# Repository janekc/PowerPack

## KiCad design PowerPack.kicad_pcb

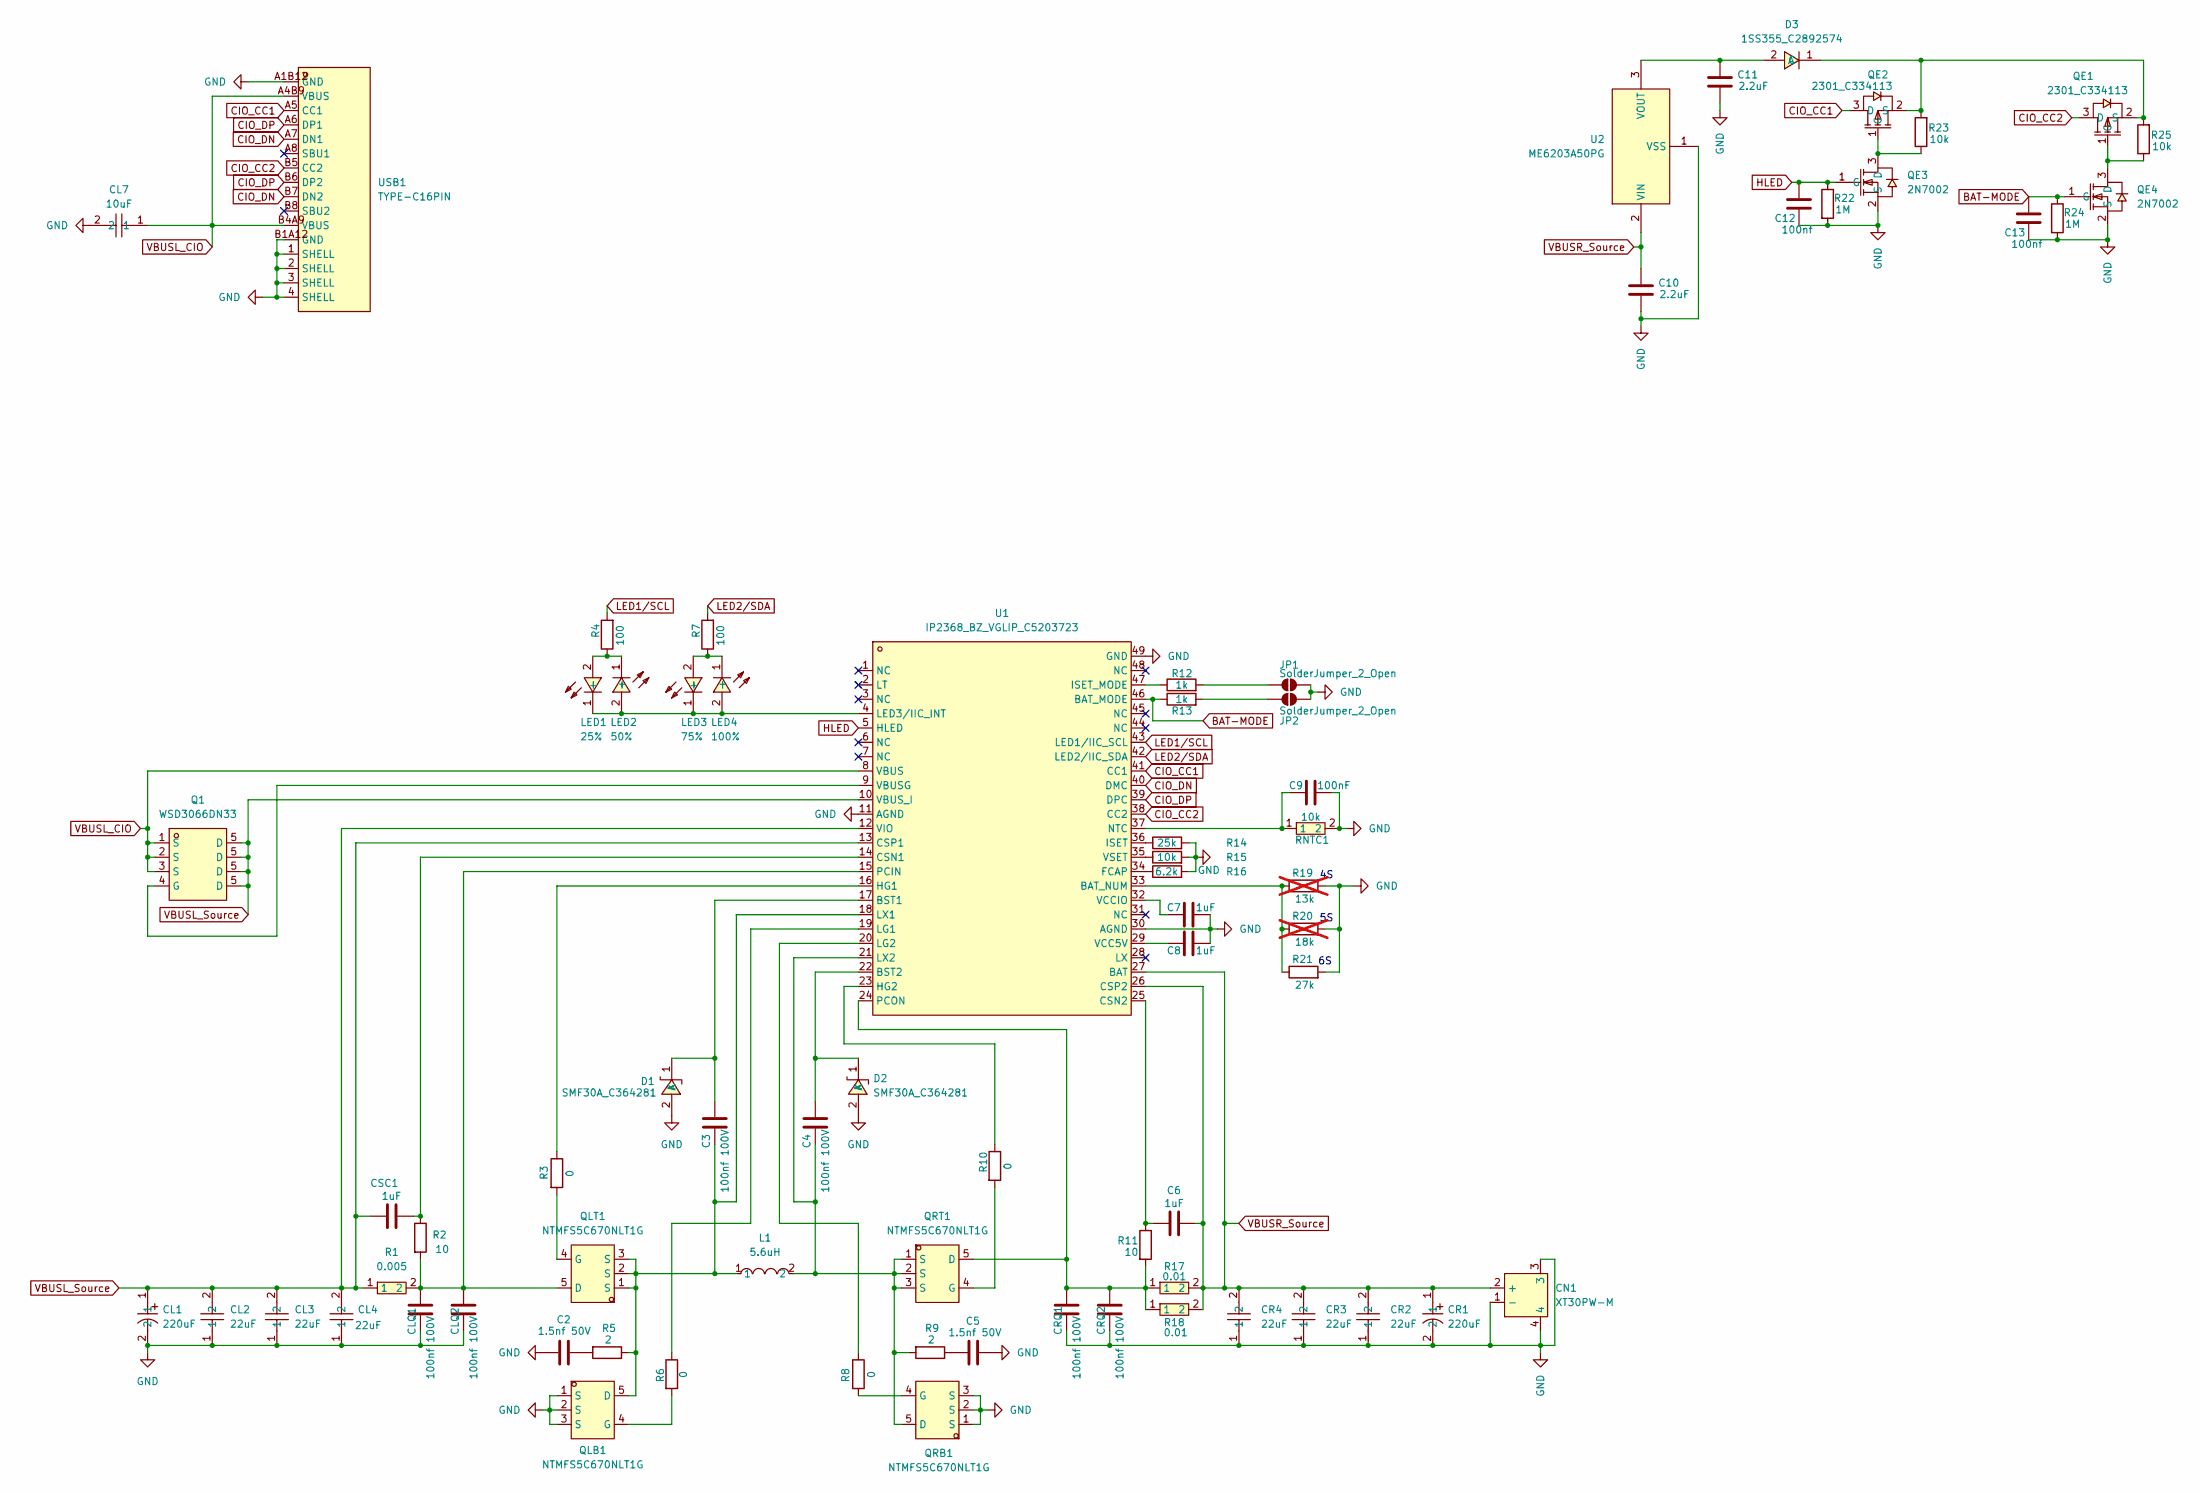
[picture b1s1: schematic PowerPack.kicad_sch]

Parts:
C2, C5: 1.5nf 50V; C_0402_1005Metric_Pad0.74x0.62mm_HandSolder
C3, C4: 100nf 100V; C_0402_1005Metric_Pad0.74x0.62mm_HandSolder
C6, C7, C8: 1uF; C_0402_1005Metric_Pad0.74x0.62mm_HandSolder
C9: 100nF; C_0603_1608Metric_Pad1.08x0.95mm_HandSolder
C10, C11: 2.2uF; C_0402_1005Metric_Pad0.74x0.62mm_HandSolder
C12, C13: 100nf; C_0402_1005Metric_Pad0.74x0.62mm_HandSolder
CL1: 220uF; CAP-TH_BD8.0-P3.50-D0.6-FD; LCSC Part C2688260
CL2, CL3, CL4: 22uF; C1210; LCSC Part C778721
CL7: 10uF; C1206; LCSC Part C76715
CLQ1, CLQ2: 100nf 100V; C_0402_1005Metric_Pad0.74x0.62mm_HandSolder
CN1: XT30PW-M; CONN-TH_XT30PW-M; LCSC Part C431092
CR1: 220uF; CAP-TH_BD8.0-P3.50-D0.6-FD; LCSC Part C2688260
CR2, CR3, CR4: 22uF; C1210; LCSC Part C778721
CRQ1, CRQ2: 100nf 100V; C_0402_1005Metric_Pad0.74x0.62mm_HandSolder
CSC1: 1uF; C_0402_1005Metric_Pad0.74x0.62mm_HandSolder
D1, D2: SMF30A_C364281; SOD-123_L2.6-W1.6-LS3.5-RD; LCSC Part C364281
D3: 1SS355_C2892574; SOD-323_L1.8-W1.3-LS2.5-RD; LCSC Part C2892574
JP1, JP2: SolderJumper_2_Open; SolderJumper-2_P1.3mm_Open_RoundedPad1.0x1.5mm
L1: 5.6uH; IND-SMD_L13.4-W12.6; LCSC Part C408522
LED1: 25%; LED0603-RD; LCSC Part C84265
LED2: 50%; LED0603-RD; LCSC Part C84265
LED3: 75%; LED0603-RD; LCSC Part C84265
LED4: 100%; LED0603-RD; LCSC Part C84265
Q1: WSD3066DN33; DFN-8_L3.3-W3.3-P0.65-BL; LCSC Part C148386
QE1, QE2: 2301_C334113; SOT-23_L2.9-W1.3-P1.90-LS2.4-BR; LCSC Part C334113
QE3, QE4: 2N7002; SOT-23-3_L2.9-W1.3-P1.90-LS2.4-BR; LCSC Part C8545
QLB1: NTMFS5C670NLT1G; DFN-5_L6.1-W5.1-P1.27-BL; LCSC Part C179626
QLT1: NTMFS5C670NLT1G; DFN-5_L6.1-W5.1-P1.27-BL; LCSC Part C179626
QRB1: NTMFS5C670NLT1G; DFN-5_L6.1-W5.1-P1.27-BL; LCSC Part C179626
QRT1: NTMFS5C670NLT1G; DFN-5_L6.1-W5.1-P1.27-BL; LCSC Part C179626
R1: 0.005; R1206; LCSC Part C723403
R2, R11: 10; R_0402_1005Metric_Pad0.72x0.64mm_HandSolder
R3, R6, R8, R10: 0; R_0603_1608Metric_Pad0.98x0.95mm_HandSolder
R4, R7: 100; R_0402_1005Metric_Pad0.72x0.64mm_HandSolder
R5, R9: 2; R_0402_1005Metric_Pad0.72x0.64mm_HandSolder
R12, R13: 1k; R_0402_1005Metric_Pad0.72x0.64mm_HandSolder
R14: 25k; R_0402_1005Metric_Pad0.72x0.64mm_HandSolder
R15, R23, R25: 10k; R_0402_1005Metric_Pad0.72x0.64mm_HandSolder
R16: 6.2k; R_0402_1005Metric_Pad0.72x0.64mm_HandSolder
R17, R18: 0.01; R1206; LCSC Part C105362
R19: 13k; R_0402_1005Metric_Pad0.72x0.64mm_HandSolder; not fitted
R20: 18k; R_0402_1005Metric_Pad0.72x0.64mm_HandSolder; not fitted
R21: 27k; R_0402_1005Metric_Pad0.72x0.64mm_HandSolder
R22, R24: 1M; R_0402_1005Metric_Pad0.72x0.64mm_HandSolder
RNTC1: 10k; R0603; LCSC Part C98220
U1: IP2368_BZ_VGLIP_C5203723; QFN-48_L7.0-W7.0-P0.50-TL-EP5.4-1; LCSC Part C5203723
U2: ME6203A50PG; SOT-89_L4.5-W2.5-P1.50-LS4.2-BR; LCSC Part C94056
USB1: TYPE-C16PIN; USB-C-SMD_TYPE-C16PIN; LCSC Part C393939

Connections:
BAT-MODE: C13.2, QE4.1 (G), R13.1, R24.1, U1.46 (BAT_MODE)
CIO_CC1: QE2.3 (D), U1.41 (CC1), USB1.A5 (CC1)
CIO_CC2: QE1.3 (D), U1.38 (CC2), USB1.B5 (CC2)
CIO_DN: U1.40 (DMC), USB1.A7 (DN1), USB1.B7 (DN2)
CIO_DP: U1.39 (DPC), USB1.A6 (DP1), USB1.B6 (DP2)
GND: C2.1, C5.2, C7.2, C8.2, C9.2, C10.1, C11.1, C12.1, C13.1, CL1.2, CL2.1, CL3.1, CL4.1, CL7.2, CLQ1.2, CLQ2.2, CN1.1 (-), CN1.3, CN1.4, CR1.2, CR2.1, CR3.1, CR4.1, CRQ1.2, CRQ2.2, D1.2 (A), D2.2 (A), JP1.2 (B), JP2.2 (B), QE3.2 (S), QE4.2 (S), QLB1.1 (S), QLB1.2 (S), QLB1.3 (S), QRB1.1 (S), QRB1.2 (S), QRB1.3 (S), R14.2, R15.2, R16.2, R19.2, R20.2, R21.2, R22.2, R24.2, RNTC1.2, U1.11 (AGND), U1.30 (AGND), U1.49 (GND), U2.1 (VSS), USB1.1 (SHELL), USB1.2 (SHELL), USB1.3 (SHELL), USB1.4 (SHELL), USB1.A1B12 (GND), USB1.B1A12 (GND)
HLED: C12.2, QE3.1 (G), R22.1, U1.5 (HLED)
LED1/SCL: R4.2, U1.43 (LED1/IIC_SCL)
LED2/SDA: R7.2, U1.42 (LED2/IIC_SDA)
unnamed: C2.2, R5.2
unnamed: C5.1, R9.1
unnamed: C3.1, D1.1 (K), U1.17 (BST1)
unnamed: C4.1, D2.1 (K), U1.22 (BST2)
unnamed: C11.2, D3.2 (A), U2.3 (VOUT)
unnamed: D3.1 (C), QE1.2 (S), QE2.2 (S), R23.2, R25.2
unnamed: JP1.1 (A), R12.2
unnamed: JP2.1 (A), R13.2
unnamed: LED1.2 (+), LED2.1 (-), R4.1
unnamed: LED1.1 (-), LED2.2 (+), LED3.1 (-), LED4.2 (+), U1.4 (LED3/IIC_INT)
unnamed: LED3.2 (+), LED4.1 (-), R7.1
unnamed: Q1.4 (G), U1.9 (VBUSG)
unnamed: QE1.1 (G), QE4.3 (D), R25.1
unnamed: QE2.1 (G), QE3.3 (D), R23.1
unnamed: C3.2, L1.1, QLB1.5 (D), QLT1.1 (S), QLT1.2 (S), QLT1.3 (S), R5.1, U1.18 (LX1)
unnamed: QLB1.4 (G), R6.2
unnamed: CLQ1.1, CLQ2.1, QLT1.5 (D), R1.2, R2.2, U1.15 (PCIN)
unnamed: QLT1.4 (G), R3.2
unnamed: C4.2, L1.2, QRB1.5 (D), QRT1.1 (S), QRT1.2 (S), QRT1.3 (S), R9.2, U1.21 (LX2)
unnamed: QRB1.4 (G), R8.2
unnamed: CRQ1.1, CRQ2.1, QRT1.5 (D), R11.2, R17.1, R18.1, U1.24 (PCON)
unnamed: QRT1.4 (G), R10.2
unnamed: R19.1, R20.1, R21.1, U1.33 (BAT_NUM)
unnamed: CSC1.2, R2.1, U1.14 (CSN1)
unnamed: C6.1, R11.1, U1.25 (CSN2)
unnamed: R16.1, U1.34 (FCAP)
unnamed: R3.1, U1.16 (HG1)
unnamed: R10.1, U1.23 (HG2)
unnamed: R14.1, U1.36 (ISET)
unnamed: R12.1, U1.47 (ISET_MODE)
unnamed: R6.1, U1.19 (LG1)
unnamed: R8.1, U1.20 (LG2)
unnamed: C9.1, RNTC1.1, U1.37 (NTC)
unnamed: C8.1, U1.29 (VCC5V)
unnamed: C7.1, U1.32 (VCCIO)
unnamed: R15.1, U1.35 (VSET)
VBUSL_CIO: CL7.1, Q1.1 (S), Q1.2 (S), Q1.3 (S), U1.8 (VBUS), USB1.A4B9 (VBUS), USB1.B4A9 (VBUS)
VBUSL_Source: CL1.1, CL2.2, CL3.2, CL4.2, CSC1.1, Q1.5 (D), R1.1, U1.10 (VBUS_I), U1.12 (VIO), U1.13 (CSP1)
VBUSR_Source: C6.2, C10.2, CN1.2 (+), CR1.1, CR2.2, CR3.2, CR4.2, R17.2, R18.2, U1.26 (CSP2), U1.27 (BAT), U2.2 (VIN)

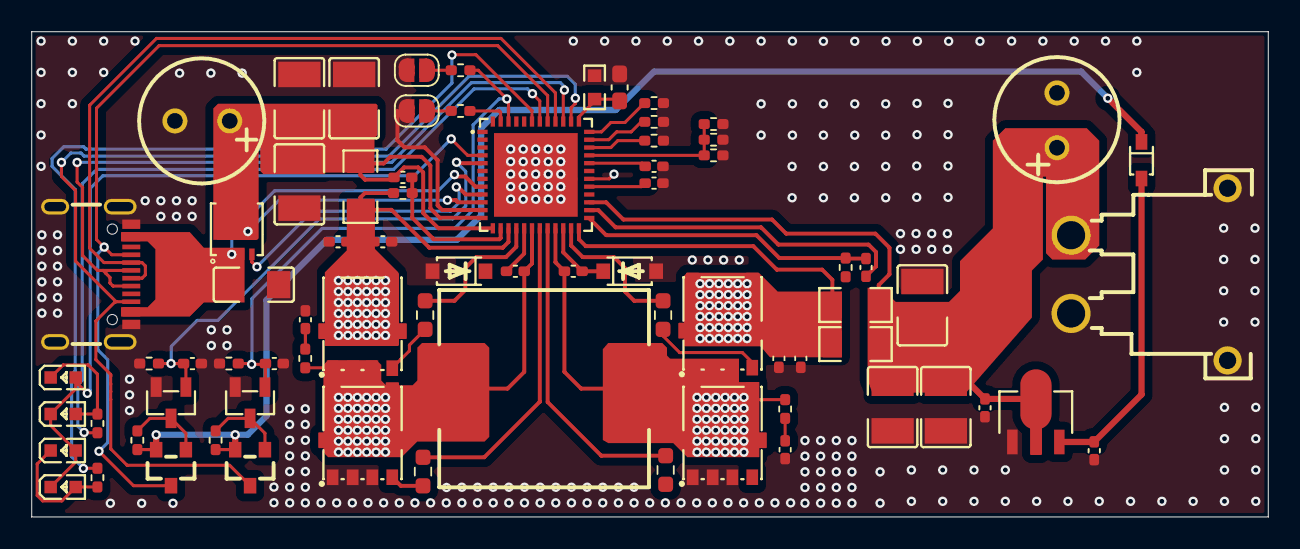
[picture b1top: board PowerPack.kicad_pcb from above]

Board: 2 copper layers, 79.0 x 31.0 mm, 75 parts (0 on the bottom side), 48 nets.

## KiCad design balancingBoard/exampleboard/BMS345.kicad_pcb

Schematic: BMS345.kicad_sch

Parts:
C1, C2, C3, C13, C14, C16, C17, C19: 1u; C0805
C4, C5, C6, C7, C8, C9, C10, C11, C12, C15, C21: 100n; C0603
C18, C22, C23: 10u; C1206
C20: 18p; C0603
D1: RED/GREEN; KingBright_KPTB
D2: Schottky; SOD-128
D3, D4: Schottky; SOT-23Z
D5: 10V; SOT-23Z
J1: CONFIG; PinHeader_2x05_P2.54mm_Vertical
J2: BATT; JSTXH_S6B
J3: DC Jack; DC_Jack
J4: EXTLED; JSTPH_3P
J5: NTC; 2P_2.54mm_header
L1: 10u; SRN1060
Logo1: ZOUDIO; ZOUDIO25mm
Q1, Q2: NMOS; SO8FLDual
R1, R3, R17, R18, R21, R25, R26: 10k; R0603
R2, R20, R22, R23, R31, R32: 1M; R0603
R4, R5, R6, R7, R8, R9, R10: 1K; R0603
R11, R16: 8m; R2512SNS
R12: 2R; R1206
R13, R14: 10K; R0603
R15, R19: 100R; R0603
R24: 3M3; R0603
R27, R33, R39: 100k; R0603
R28: 75K; R0603
R29: 10R; R0603
R30, R38: 39m; R1206
R34, R35, R37: 249k; R0603
R36: 33M; R0603
TP1: BATT+; Pad_6mm
TP2: BATT-; Pad_6mm
TP3: PACK+; Pad_6mm
TP4: PACK-; Pad_6mm
U1: BQ24650; QFN16
U2: BQ77915; TSSOP-24

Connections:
+24V: D1.1, D1.3, D2.2 (A), J3.1, J4.2, R12.2, R22.2
/AVDD: C13.1, J1.6, U2.2
/BATT-: R11.2, R15.1, R16.2, TP2.1
/CCFG: J1.4, U2.20
/PACK+: C18.1, C19.2, C20.1, C21.2, C23.1, R30.2, R31.2, R36.2, R38.2, TP1.1, TP3.1, U1.9
/TS: R13.1, R14.2, U1.4
/VC3: C5.2, C6.1, J1.10, R7.1, U2.5
/VC4: C4.2, C5.1, J1.7, J1.8, R6.1, U2.4
/VC5: C4.1, J1.9, R5.1, U2.3
/VFB: C20.2, J1.3, R31.1, R33.2, R36.1, U1.8
/VREF: C14.2, R13.2, U1.6, U1.7
GND: C3.2, C8.2, C9.1, C11.1, C12.2, C13.2, J1.2, J2.1, J5.2, R10.2, R26.1, R27.1, U2.9, U2.16, U2.23, U2.24
GNDPWR: C1.1, C2.1, C14.1, C16.2, C17.2, C18.2, C19.1, C22.2, C23.2, D5.2 (A), J3.2, J3.3, Q1.5, Q2.2, R2.1, R14.1, R24.1, R28.1, R32.1, R34.2, R37.2, R39.1, TP4.1, U1.11, U1.17
unnamed: C1.2, C2.2, R12.1
unnamed: C3.1, R4.1, R25.1, U2.1
unnamed: C6.2, C7.1, R8.1, U2.6
unnamed: C7.2, C8.1, R9.1, U2.7
unnamed: C9.2, R10.1, U2.8
unnamed: C10.1, C11.2, R19.2, U2.11
unnamed: C10.2, C12.1, R15.2, U2.10
unnamed: C15.1, D3.1 (K), U1.16
unnamed: C15.2, L1.1, Q2.4, Q2.5, U1.14
unnamed: C16.1, R29.1, U1.1
unnamed: C17.1, D3.2 (A), U1.12
unnamed: C21.1, L1.2, R30.1, R38.1, U1.10
unnamed: C22.1, D2.1 (K), Q2.6, R29.2
unnamed: D1.2, J4.3, R17.2
unnamed: D1.4, J4.1, R18.2
unnamed: D4.1 (K), D5.1 (K), Q1.1, R23.1, R24.2
unnamed: D4.2 (A), R1.1, R23.2
unnamed: J1.1, R35.1
unnamed: J1.5, R34.1
unnamed: J2.2, R9.2
unnamed: J2.3, R8.2
unnamed: J2.4, R7.2
unnamed: J2.5, R6.2
unnamed: J2.6, R4.2, R5.2
unnamed: J5.1, R3.1, R26.2, U2.18
unnamed: Q1.2, R11.1, R16.1, R19.1, R20.1
unnamed: Q1.3, R20.2, R21.1
unnamed: Q1.4, Q1.6
unnamed: Q2.1, U1.15
unnamed: Q2.3, U1.13
unnamed: R1.2, U2.13
unnamed: R2.2, R32.2, U2.14
unnamed: R3.2, U2.19
unnamed: R17.1, U1.3
unnamed: R18.1, U1.5
unnamed: R21.2, U2.12
unnamed: R22.1, R28.2, U1.2
unnamed: R25.2, U2.22
unnamed: R27.2, U2.17
unnamed: R33.1, R39.2
unnamed: R35.2, R37.1

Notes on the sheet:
CEL3
CEL1
CEL4
Default charge voltage is 4.2V per cell populate R36 for 4.1V per cell
CEL2
Default charge current is 1A Populate R38 for 2A
=17.2V
Charger
CHARGER<->PACK
Configuration header (refer to manual)
Protection
CEL5

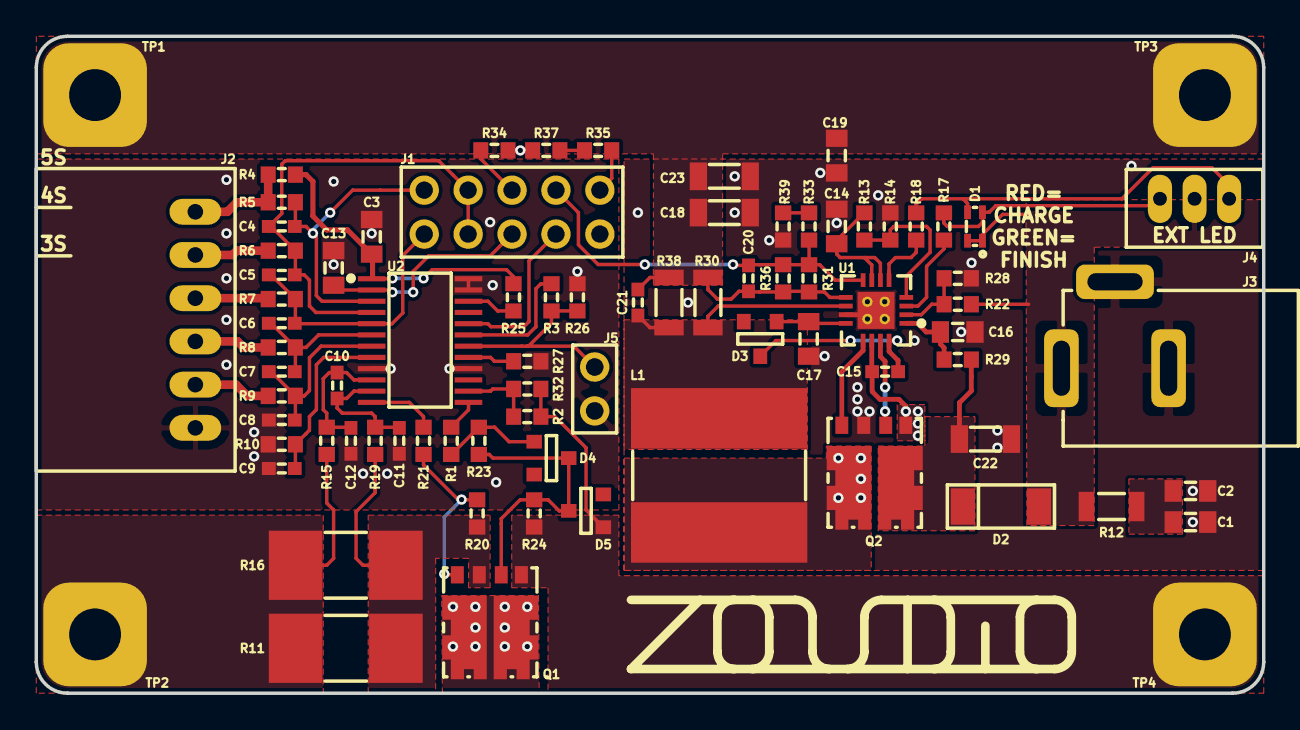
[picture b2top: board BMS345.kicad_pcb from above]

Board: 2 copper layers, 71.0 x 38.0 mm, 82 parts (0 on the bottom side), 54 nets.

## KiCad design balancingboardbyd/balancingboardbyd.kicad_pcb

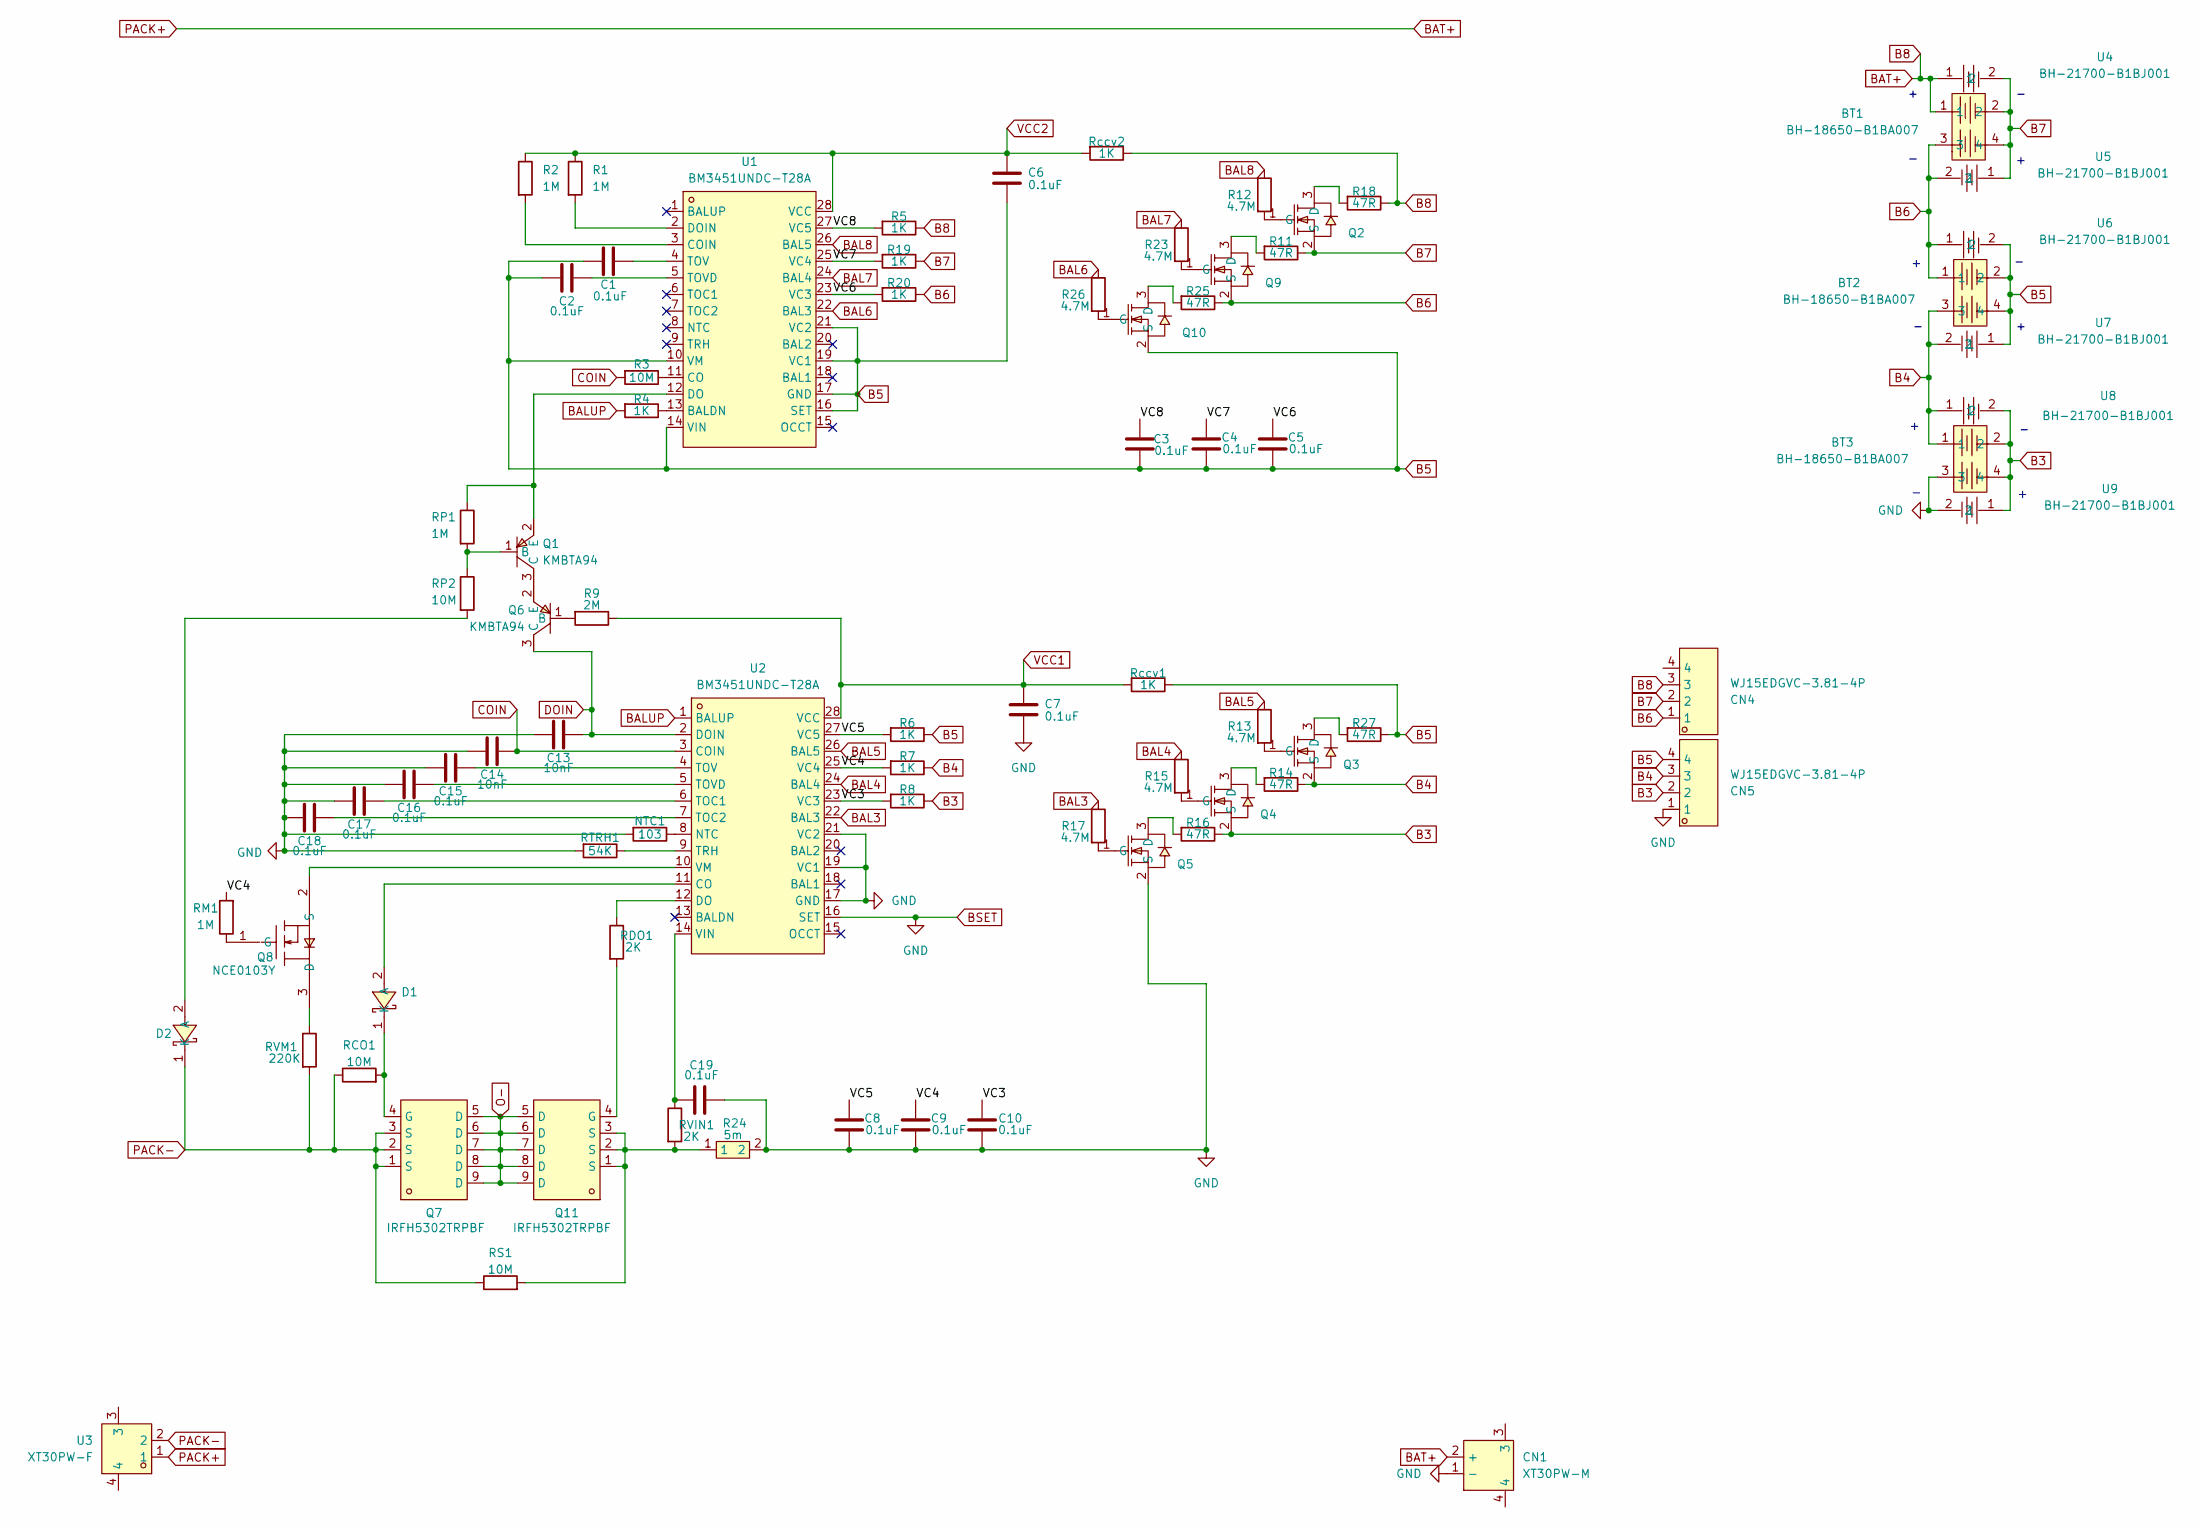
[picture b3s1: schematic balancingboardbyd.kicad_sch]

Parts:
BT1, BT2, BT3: BH-18650-B1BA007; BAT-SMD_BH-18650-B1BA007; LCSC Part C6937126
C1, C2, C3, C4, C5, C6, C7, C8, C9, C10, C15, C16, C17, C18, C19: 0.1uF; C_0603_1608Metric_Pad1.08x0.95mm_HandSolder
C13, C14: 10nF; C_0603_1608Metric_Pad1.08x0.95mm_HandSolder
CN1: XT30PW-M; CONN-TH_XT30PW-M; LCSC Part C431092
CN4, CN5: WJ15EDGVC-3.81-4P; CONN-TH_4P-P3.81_WJ2EDGVC-3.81-4P; LCSC Part C8410
D1, D2: B5819W_C917036; SOD-123_L2.8-W1.8-LS3.7-RD-1; LCSC Part C917036
NTC1: 103; R_0603_1608Metric_Pad0.98x0.95mm_HandSolder
Q1, Q6: KMBTA94; SOT-23-3_L2.9-W1.3-P1.90-LS2.4-BR; LCSC Part C489166
Q2, Q3, Q4, Q5, Q9, Q10: SI2302A-TP; SOT-23-3_L2.9-W1.3-P1.90-LS2.4-BR; LCSC Part C668996
Q7, Q11: IRFH5302TRPBF; PQFN-8_L6.0-W5.0-P1.27-LS6.0-BL; LCSC Part C148153
Q8: NCE0103Y; SOT-23-3_L2.9-W1.6-P1.90-LS2.8-BR; LCSC Part C153001
R1, R2: 1M; R_0603_1608Metric_Pad0.98x0.95mm_HandSolder
R3: 10M; R_0603_1608Metric_Pad0.98x0.95mm_HandSolder
R4, R5, R6, R7, R8, R19, R20: 1K; R_0603_1608Metric_Pad0.98x0.95mm_HandSolder
R9: 2M; R_0603_1608Metric_Pad0.98x0.95mm_HandSolder
R11, R14, R16, R18, R25, R27: 47R; R_1206_3216Metric_Pad1.30x1.75mm_HandSolder
R12, R13, R15, R17, R23, R26: 4.7M; R_0603_1608Metric_Pad0.98x0.95mm_HandSolder
R24: 5m; R_2512_6332Metric_Pad1.40x3.35mm_HandSolder; LCSC Part C5123656
RCO1: 10M; R_0603_1608Metric_Pad0.98x0.95mm_HandSolder
RDO1: 2K; R_0603_1608Metric_Pad0.98x0.95mm_HandSolder
RM1: 1M; R_0603_1608Metric_Pad0.98x0.95mm_HandSolder
RP1: 1M; R_0603_1608Metric_Pad0.98x0.95mm_HandSolder
RP2: 10M; R_0603_1608Metric_Pad0.98x0.95mm_HandSolder
RS1: 10M; R_0603_1608Metric_Pad0.98x0.95mm_HandSolder
RTRH1: 54K; R_0603_1608Metric_Pad0.98x0.95mm_HandSolder
RVIN1: 2K; R_0603_1608Metric_Pad0.98x0.95mm_HandSolder
RVM1: 220K; R_0603_1608Metric_Pad0.98x0.95mm_HandSolder
Rccv1, Rccv2: 1K; R_0603_1608Metric_Pad0.98x0.95mm_HandSolder
U1, U2: BM3451UNDC-T28A; TSSOP-28_L9.7-W4.4-P0.65-LS6.4-BL; LCSC Part C94597
U3: XT30PW-F; CONN-TH_XT30PW-F-1; LCSC Part C2913282
U4, U5, U6, U7, U8, U9: BH-21700-B1BJ001; BAT-SMD_L82.5.5-W25-BH-21700-B1BJ001; LCSC Part C20606791

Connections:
/VC3: C10.2, R8.2, U2.23 (VC3)
/VC4: C9.2, R7.2, RM1.2, U2.25 (VC4)
/VC5: C8.2, R6.2, U2.27 (VC5)
/VC6: C5.2, R20.2, U1.23 (VC3)
/VC7: C4.2, R19.2, U1.25 (VC4)
/VC8: C3.2, R5.2, U1.27 (VC5)
B3: BT3.2, BT3.4, CN5.2, Q4.2 (S), R8.1, R16.1, U8.2, U9.1
B4: BT2.3, BT3.1, CN5.3, Q3.2 (S), R7.1, R14.1, U7.2, U8.1
B5: BT2.2, BT2.4, C1.1, C2.1, C3.1, C4.1, C5.1, C6.1, CN5.4, Q10.2 (S), R6.1, R27.1, Rccv1.1, U1.10 (VM), U1.14 (VIN), U1.16 (SET), U1.17 (GND), U1.19 (VC1), U1.21 (VC2), U6.2, U7.1
B6: BT1.3, BT2.1, CN4.1, Q9.2 (S), R20.1, R25.1, U5.2, U6.1
B7: BT1.2, BT1.4, CN4.2, Q2.2 (S), R11.1, R19.1, U4.2, U5.1
B8: BT1.1, CN1.2 (+), CN4.3, R5.1, R18.1, Rccv2.1, U3.1, U4.1
BAL3: R17.1, U2.22 (BAL3)
BAL4: R15.1, U2.24 (BAL4)
BAL5: R13.1, U2.26 (BAL5)
BAL6: R26.1, U1.22 (BAL3)
BAL7: R23.1, U1.24 (BAL4)
BAL8: R12.1, U1.26 (BAL5)
BALUP: R4.2, U2.1 (BALUP)
BSET: BT3.3, C7.1, C8.1, C9.1, C10.1, C13.1, C14.1, C15.1, C16.1, C17.1, C18.1, C19.2, CN1.1 (-), CN5.1, NTC1.2, Q5.2 (S), R24.2, RTRH1.2, U2.16 (SET), U2.17 (GND), U2.19 (VC1), U2.21 (VC2), U9.2
COIN: C14.2, R3.2, U2.3 (COIN)
DOIN: C13.2, Q6.3 (C), U2.2 (DOIN)
unnamed: D1.2 (A), U2.11 (CO)
unnamed: D1.1 (K), Q7.4 (G), RCO1.2
unnamed: D2.2 (A), RP2.2
unnamed: Q1.1 (B), RP1.2, RP2.1
unnamed: Q1.3 (C), Q6.2 (E)
unnamed: Q1.2 (E), RP1.1, U1.12 (DO)
unnamed: Q2.3 (D), R18.2
unnamed: Q2.1 (G), R12.2
unnamed: Q3.3 (D), R27.2
unnamed: Q3.1 (G), R13.2
unnamed: Q4.3 (D), R14.2
unnamed: Q4.1 (G), R15.2
unnamed: Q5.3 (D), R16.2
unnamed: Q5.1 (G), R17.2
unnamed: Q6.1 (B), R9.2
unnamed: Q8.3 (D), RVM1.1
unnamed: Q8.1 (G), RM1.1
unnamed: Q8.2 (S), U2.10 (VM)
unnamed: Q9.3 (D), R11.2
unnamed: Q9.1 (G), R23.2
unnamed: Q10.3 (D), R25.2
unnamed: Q10.1 (G), R26.2
unnamed: Q11.4 (G), RDO1.2
unnamed: Q11.1 (S), Q11.2 (S), Q11.3 (S), R24.1, RS1.2, RVIN1.2
unnamed: R4.1, U1.13 (BALDN)
unnamed: R3.1, U1.11 (CO)
unnamed: R2.2, U1.3 (COIN)
unnamed: R1.2, U1.2 (DOIN)
unnamed: C1.2, U1.4 (TOV)
unnamed: C2.2, U1.5 (TOVD)
unnamed: RDO1.1, U2.12 (DO)
unnamed: NTC1.1, U2.8 (NTC)
unnamed: C17.2, U2.6 (TOC1)
unnamed: C18.2, U2.7 (TOC2)
unnamed: C15.2, U2.4 (TOV)
unnamed: C16.2, U2.5 (TOVD)
unnamed: RTRH1.1, U2.9 (TRH)
unnamed: C19.1, RVIN1.1, U2.14 (VIN)
O-: Q7.5 (D), Q7.6 (D), Q7.7 (D), Q7.8 (D), Q7.9 (D), Q11.5 (D), Q11.6 (D), Q11.7 (D), Q11.8 (D), Q11.9 (D)
PACK-: D2.1 (K), Q7.1 (S), Q7.2 (S), Q7.3 (S), RCO1.1, RS1.1, RVM1.2, U3.2
VCC1: C7.2, R9.1, Rccv1.2, U2.28 (VCC)
VCC2: C6.2, R1.1, R2.1, Rccv2.2, U1.28 (VCC)

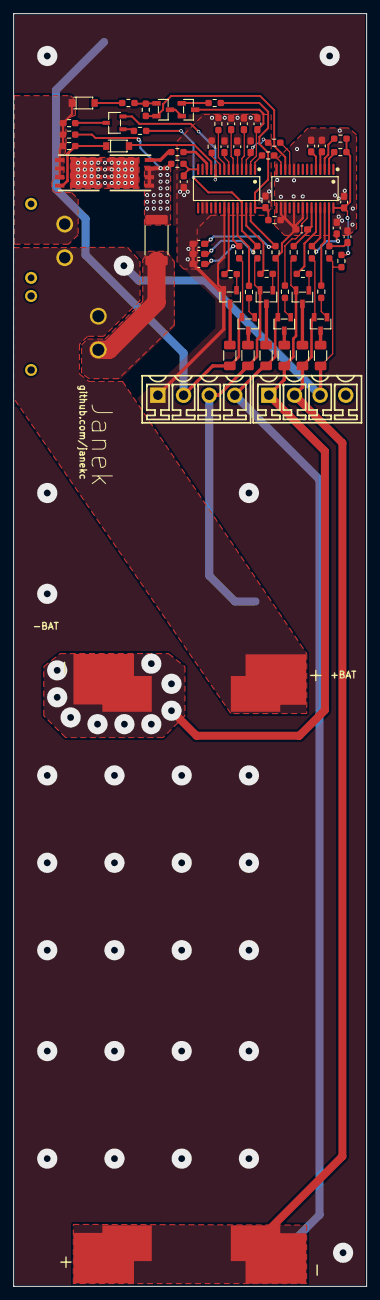
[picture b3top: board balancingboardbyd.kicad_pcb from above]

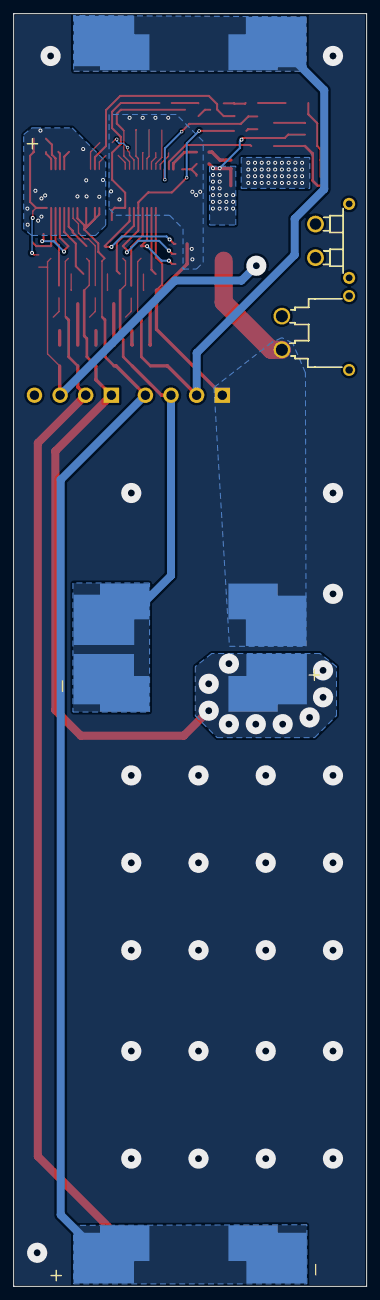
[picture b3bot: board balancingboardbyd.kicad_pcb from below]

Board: 2 copper layers, 52.5 x 189.3 mm, 81 parts (8 on the bottom side), 64 nets.

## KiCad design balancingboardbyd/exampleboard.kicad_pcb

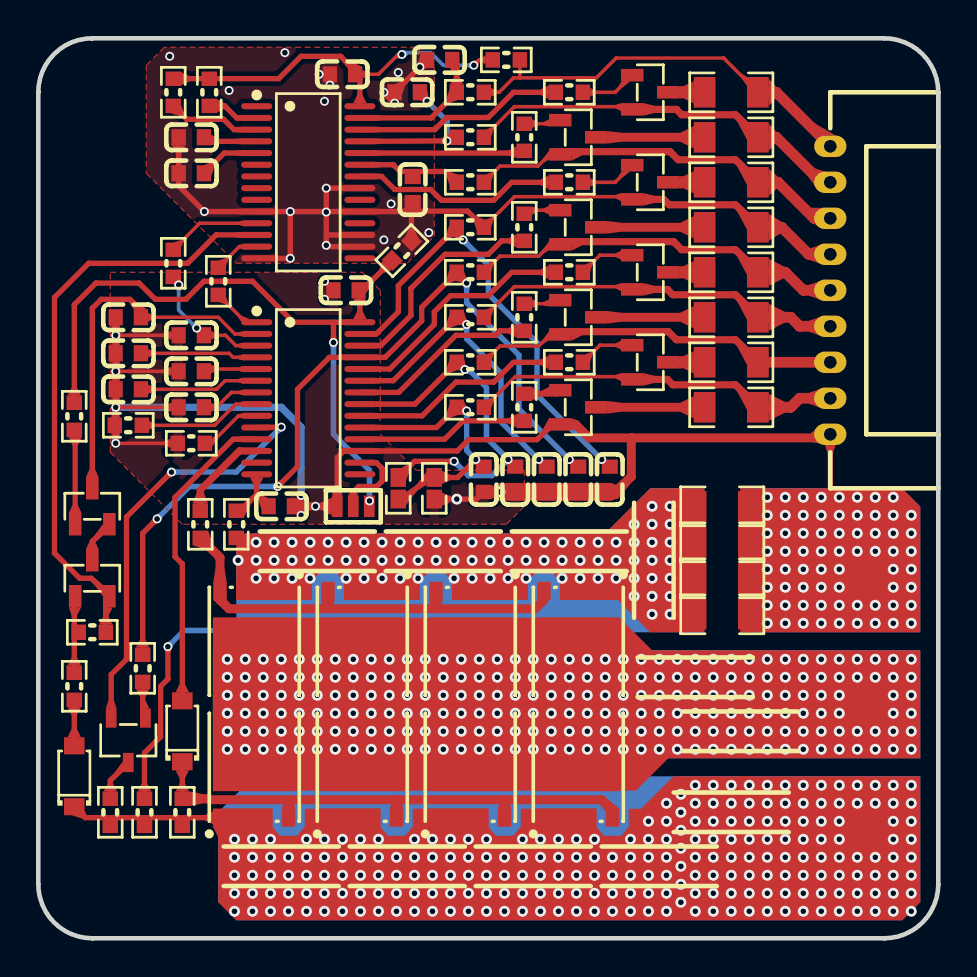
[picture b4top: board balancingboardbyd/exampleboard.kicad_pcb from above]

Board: 2 copper layers, 50.0 x 50.0 mm, 102 parts (0 on the bottom side), 75 nets.

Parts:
C1, C2, C3, C4, C5, C7, C8, C9, C10, C11, C13, C14, C20, C21, C22: 0.1UF; C0603
C6, C18: C0603
C12, C15: 10NF; C0603
D1, D2: B5819W_C917036 COPY; SOD-123_L2.8-W1.8-LS3.7-RD
NTC: 103; R0603
Q1, Q3, Q14, Q15, Q16, Q17, Q18, Q19: 5x6 NMOS; 5*6 NMOS
Q2, Q4, Q5, Q6, Q7, Q8, Q9, Q10: SI2302A-TP; SOT-23-3_L2.9-W1.3-P1.90-LS2.4-BR
Q11, Q13: KMBTA94; SOT-23-3_L2.9-W1.3-P1.90-LS2.4-BR
Q12: NCE0103; SOT-23-3_L2.9-W1.6-P1.90-LS2.8-BR
R1, R36, R37, R38: R010; R1206
R2, R3, R4, R5, R6, R32, R33, R34: 1k; R0603
R7, R8, R9, R10, R17, R20, R30, R31: 47r; R1206
R11, R12, R13, R14, R18, R19, R24, R25: 4.7M; R0603
R22, R23: 1M; R0603
R26: 1K; R0603
R35: 2M; R0603
RCO, RCO1: 10M; R0603
RDO: 2K; R0603
RM1: 1M; R0603
RP: 1M; R0603
RP1: 10M; R0603
RS: 10M; R0603
RTRH: 54K; R0603
RVCC, RVCC2: 1K; R0603
RVIN: 2K; R0603
RVM: 220K; R0603
U1, U2: BM3451UNDC-T28A; TSSOP-28_L9.7-W4.4-P0.65-LS6.4-BL
U3: 12短接点
U4, U5: 0603短接点
U6, U7, U8, U9, U10, U11, U12, U13, U14, U15, U16: 过流紫铜片6.3*1.5
U17: PH2.0-9A-WR

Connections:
B1: Q5.2, R2.1, R10.2, U17.2
B2: Q6.2, R3.1, R9.2, U17.3
B3: Q7.2, R4.1, R8.2, U17.4
B4: Q8.2, R5.1, R7.2, U17.5
B5: C13.2, C14.2, C18.1, C20.1, C21.1, C22.1, Q10.2, R6.1, R17.2, RVCC.2, U2.10, U2.14, U2.16, U2.17, U2.19, U2.21, U17.6
B6: Q9.2, R30.2, R34.1, U17.7
B7: Q4.2, R31.2, R33.1, U17.8
B8: R20.2, R32.1, RVCC2.2, U17.9
BAL1: R11.1, U1.18
BAL2: R12.1, U1.20
BAL3: R13.1, U1.22
BAL4: R14.1, U1.24
BAL5: R18.1, U1.26
BAL6: R25.1, U2.22
BAL7: R24.1, U2.24
BAL8: R19.1, U2.26
BALUP: R26.2, U1.1
BSET: U1.16, U3.1
C13_1: C13.1, U2.4
C14_1: C14.1, U2.5
COIN: C12.1, RCO1.1, U1.3
DOIN: C15.1, Q11.3, U1.2
GND: C1.1, C2.1, C3.1, C4.1, C5.1, C6.1, C7.1, C8.2, C9.2, C10.2, C11.2, C12.2, C15.2, NTC.1, Q2.2, R1.2, R36.2, R37.2, R38.2, RTRH.1, U1.17, U3.3, U4.1, U17.1
O-: Q1.3, Q3.3, Q14.3, Q15.3, Q16.3, Q17.3, Q18.3, Q19.3, U13.1, U14.1
P-: D2.1, Q1.1, Q15.1, Q17.1, Q19.1, RCO.1, RS.1, RVM.1, U9.1, U10.1, U11.1, U12.1, U16.1
Q1_2: D1.1, Q1.2, Q15.2, Q17.2, Q19.2, RCO.2
Q4_1: Q4.1, R19.2
Q4_3: Q4.3, R20.1
Q9_1: Q9.1, R24.2
Q9_3: Q9.3, R31.1
Q10_1: Q10.1, R25.2
Q10_3: Q10.3, R30.1
Q11_1: Q11.1, R35.2
Q11_2: Q11.2, Q13.3
Q12_1: Q12.1, RM1.1
Q13_1: Q13.1, RP.1, RP1.2
R1_1: Q3.1, Q14.1, Q16.1, Q18.1, R1.1, R36.1, R37.1, R38.1, RS.2, RVIN.2, U6.1, U7.1, U8.1, U15.1
R7_1: Q7.3, R7.1
R8_1: Q6.3, R8.1
R9_1: Q5.3, R9.1
R10_1: Q2.3, R10.1
R11_2: Q2.1, R11.2
R12_2: Q5.1, R12.2
R13_2: Q6.1, R13.2
R14_2: Q7.1, R14.2
R17_1: Q8.3, R17.1
R18_2: Q8.1, R18.2
R22_2: R22.2, U2.3
R23_2: R23.2, U2.2
RCO1_2: RCO1.2, U2.11
RDO_2: Q3.2, Q14.2, Q16.2, Q18.2, RDO.2
RP1_1: D2.2, RP1.1
RVM_2: Q12.3, RVM.2
U1_4: C11.1, U1.4
U1_5: C10.1, U1.5
U1_6: C9.1, U1.6
U1_7: C8.1, U1.7
U1_8: NTC.2, U1.8
U1_9: RTRH.2, U1.9
U1_10: Q12.2, U1.10
U1_11: D1.2, U1.11
U1_12: RDO.1, U1.12
U1_14: C7.2, RVIN.1, U1.14
U2_12: Q13.2, RP.2, U2.12
U2_13: R26.1, U2.13
VC1: C2.2, R2.2, U1.19, U4.2, U5.1
VC2: C5.2, R3.2, U1.21, U5.2
VC3: C4.2, R4.2, U1.23
VC4: C3.2, R5.2, RM1.2, U1.25
VC5: C1.2, R6.2, U1.27
VC6: C20.2, R34.2, U2.23
VC7: C21.2, R33.2, U2.25
VC8: C22.2, R32.2, U2.27
VCC1: C6.2, R35.1, RVCC.1, U1.28, U3.2
VCC2: C18.2, R22.1, R23.1, RVCC2.1, U2.28

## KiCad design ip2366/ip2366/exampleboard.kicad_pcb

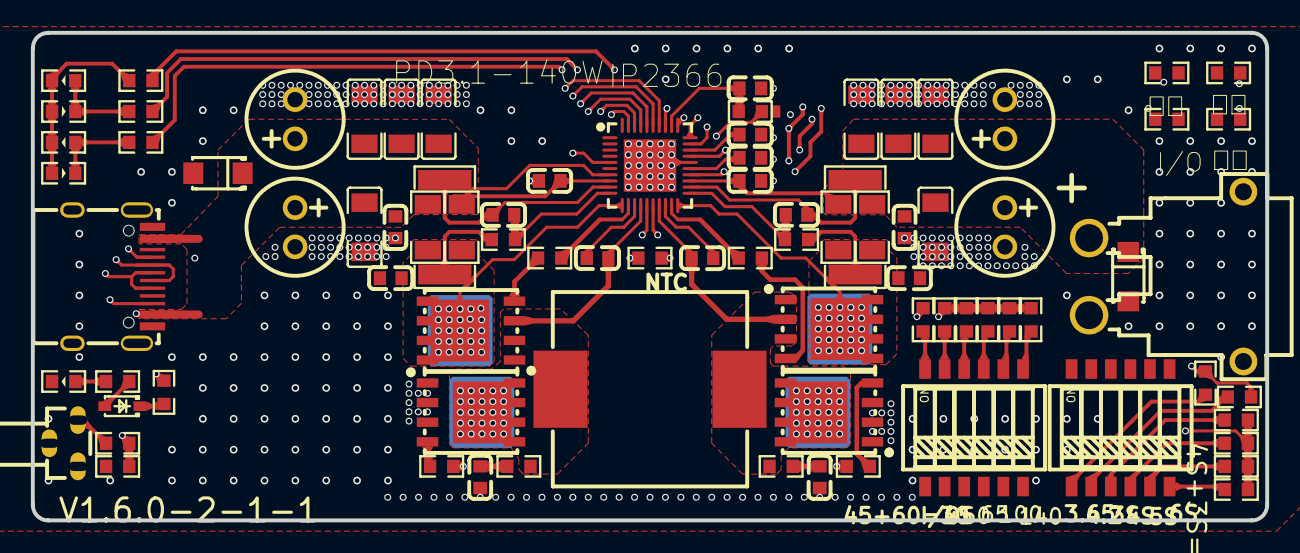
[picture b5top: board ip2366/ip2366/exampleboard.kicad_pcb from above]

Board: 4 copper layers, 80.0 x 31.6 mm, 85 parts (0 on the bottom side), 56 nets.

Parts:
C3, C4, C22, C24: 100UF; CAP-TH_BD6.3-P2.50-D1.0-FD
C6, C7, C19, C20, C29, C30, C31, C32: 22UF; C1206
C8, C15, C16, C17: 2.2UF; C0603
C9, C18: 1UF; C0603
C10, C11, C14, C25, C26, C27, C28: 100NF; C0603
C12, C13: 3.3NF; C0603
D1: SMF30A-HM3-18; DO-219AB_L2.8-W1.8-LS3.7-FD
D2: SMF30A; DO-219AB_L2.8-W1.8-LS3.7-FD
D3: MM3Z5V1_C19077455; SOD-323_L1.7-W1.3-LS2.6-RD
L1: 10UH; SMD-1265
LED1, LED2, LED3, LED4, LED5: LED-0603_R; 0603LED
NTC: 10K; R0603
Q3, Q4, Q5, Q6: AER4061BE; DFN-8_L5.2-W5.6-P1.27-LS6.1-BL
R1, R2: 100R; R0603
R3, R9, R10, R13, R14, R24: 0R; R0603
R4: 43K; R0603
R5, R23: 10K; R0603
R6, R7, R16, R17: 5mr; R1206
R8, R15: 10R; R0603
R11, R12: 2R; R0603
R18, R26, R32, R34: 9.1K; R0603
R19, R29: 27K; R0603
R20, R27, R35: 13K; R0603
R21, R30: 1K; R0603
R22: 3.24K; R0603
R25, R33: 6.2K; R0603
R28, R36: 18K; R0603
R31: 3.6K; R0603
R37, R38: 5mr; R2512
SW2, SW3: ON; SW-SMD_12P-L9.2-W5.4-P1.27-LS8.5
U1: TYPE-C16P; TYPE-C-16P
U2: IP2366
U3: 轻触开关-边3脚
U4: XT30PW-M（凹）; XT30PW-M

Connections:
BAT: C17.1, C18.2, C19.1, C20.1, C22.1, C24.1, C26.2, C31.1, C32.1, D2.2, R16.2, R17.2, R38.2, U2.22, U2.23, U3.2, U4.2
BAT_NUM: R20.1, R33.2, R34.2, R35.2, R36.2, U2.27
C9_1: C9.1, R8.2, U2.10
C10_1: C10.1, U2.13
C11_1: C11.1, U2.18
C12_2: C12.2, R11.1
C13_2: C13.2, R12.1
C15_1: C15.1, U2.28
C16_1: C16.1, U2.25
C18_1: C18.1, R15.2, U2.21
CC1: U1.A5, U2.37
CC2: U1.B5, U2.34
CC_BDO: R21.1, R30.2, U2.24
D3_1: D3.1, R24.1
D3_2: D3.2, R23.2
DM: U1.A7, U1.B7, U2.36
DP: U1.A6, U1.B6, U2.35
EN: R4.1, R5.1, U2.33
GND: C3.2, C4.2, C6.2, C7.2, C8.1, C12.1, C13.1, C14.2, C15.2, C16.2, C17.2, C19.2, C20.2, C22.2, C24.2, C25.1, C26.1, C27.1, C28.1, C29.2, C30.2, C31.2, C32.2, D1.1, D2.1, LED5.2, NTC.2, Q5.1, Q5.2, Q5.3, Q6.1, Q6.2, Q6.3, R5.2, R18.2, R19.2, R20.2, R21.2, SW2.1, SW2.2, SW2.3, SW2.4, SW2.5, SW2.6, SW3.7, SW3.8, SW3.9, SW3.10, SW3.11, SW3.12, U1.13, U1.14, U1.15, U1.16, U1.A1B12, U1.B1A12, U2.26, U2.41, U3.3, U4.1, U4.3, U4.4
HG1: R9.1, U2.12
HG2: R13.1, U2.19
LED1: R1.1, U2.39
LED2: R2.2, U2.38
LED2_2: LED1.1, LED2.2, R1.2
LED3: R3.1, U2.31
LED4_1: LED1.2, LED2.1, LED3.2, LED4.1, R3.2
LED4_2: LED3.1, LED4.2, R2.1
LED5_1: LED5.1, R23.1
LG1: R10.2, U2.15
LG2: R14.2, U2.16
NTC: C14.1, R22.1, U2.32
NTC_1: NTC.1, R22.2
PSET: R19.1, R25.1, R26.1, R27.1, R28.1, R29.1, U2.29
Q3_1: C10.2, L1.1, Q3.1, Q3.2, Q3.3, Q5.5, Q5.6, Q5.7, Q5.8, Q5.9, R11.2, U2.14
Q3_4: Q3.4, R9.2
Q3_5: C27.2, Q3.5, Q3.6, Q3.7, Q3.8, Q3.9, R6.2, R7.2, R8.1, R37.2, U2.11
Q4_1: C11.2, L1.2, Q4.1, Q4.2, Q4.3, Q6.5, Q6.6, Q6.7, Q6.8, Q6.9, R12.2, U2.17
Q4_4: Q4.4, R13.2
Q4_5: C28.2, Q4.5, Q4.6, Q4.7, Q4.8, Q4.9, R15.1, R16.1, R17.1, R38.1, U2.20
Q5_4: Q5.4, R10.1
Q6_4: Q6.4, R14.1
R4_2: R4.2, U3.1
R26_2: R26.2, SW2.10
R27_2: R27.2, SW2.9
R28_2: R28.2, SW2.8
R29_2: R29.2, SW2.7
R30_1: R30.1, SW2.12
R33_1: R33.1, SW3.3
R34_1: R34.1, SW3.4
R35_1: R35.1, SW3.5
R36_1: R36.1, SW3.6
SW2_11: R25.2, SW2.11
SW3_1: R31.1, SW3.1
SW3_2: R32.1, SW3.2
VBUS: C3.1, C4.1, C6.1, C7.1, C8.2, C9.2, C25.2, C29.1, C30.1, D1.2, R6.1, R7.1, R24.2, R37.1, U1.A4B9, U1.B4A9, U2.5, U2.7, U2.8, U2.9
VSET: R18.1, R31.2, R32.2, U2.30
